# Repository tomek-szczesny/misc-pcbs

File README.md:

# misc-pcbs
Miscellaneous PCB designs

## BuLDOck

A Buck converter with LDO following it, for super clean DC output voltage. Recommended for noise sensitive applications such as audio equipment.

Designed on a single layer and with no holes, suitable for aluminum PCBs.

## ICE40HX8K-EVB Breadboard

A multipurpose breadboard that fits directly into Olimex FPGA devkit.

## PowerDistributor

A 2-layer board for DC voltage distribution. Designed for SBC cluster but might be used for anything.

Two M4 screw holes were designed to handle 30A power input. Eight pairs of screw terminals would usually serve as outputs, but that's not the law.

A center area is for properly rated capacitors - make more sense in low current applications.

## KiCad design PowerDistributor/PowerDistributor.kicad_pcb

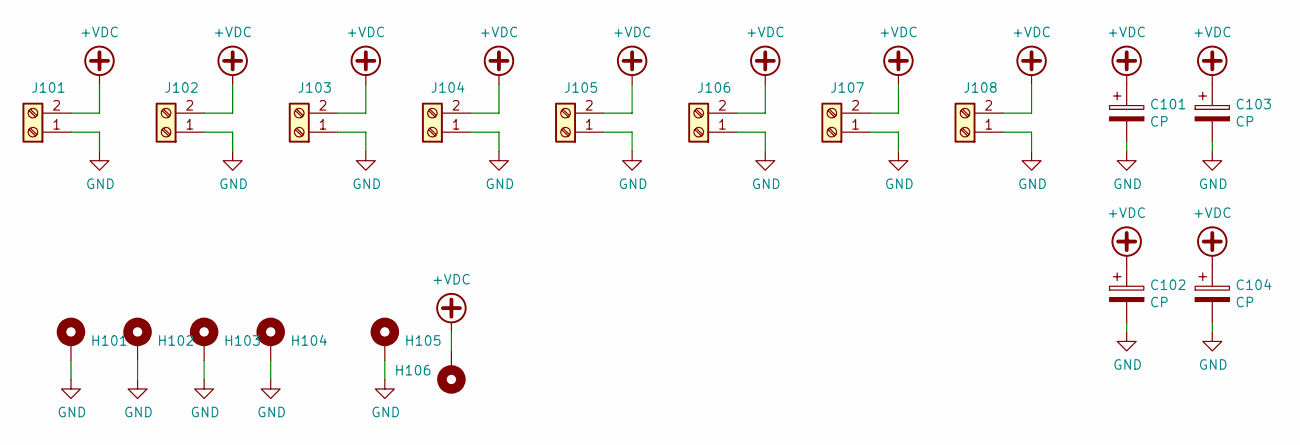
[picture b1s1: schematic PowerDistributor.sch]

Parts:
C101, C102, C103, C104: CP; CP_Radial_D10.0mm_P5.00mm
H101, H102, H103, H104: MountingHole_Pad; MountingHole_3mm_Pad_TopOnly
H105, H106: MountingHole_Pad; MountingHole_4.3mm_M4_Pad_TopBottom
J101, J102, J103, J104, J105, J106, J107, J108: Screw_Terminal_01x02; TerminalBlock_Altech_AK300-2_P5.00mm

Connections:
+VDC: C101.1, C102.1, C103.1, C104.1, H106.1, J101.2, J102.2, J103.2, J104.2, J105.2, J106.2, J107.2, J108.2
GND: C101.2, C102.2, C103.2, C104.2, H101.1, H102.1, H103.1, H104.1, H105.1, J101.1, J102.1, J103.1, J104.1, J105.1, J106.1, J107.1, J108.1

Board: 2 copper layers, 18 parts (0 on the bottom side), 2 nets, no tracks yet.

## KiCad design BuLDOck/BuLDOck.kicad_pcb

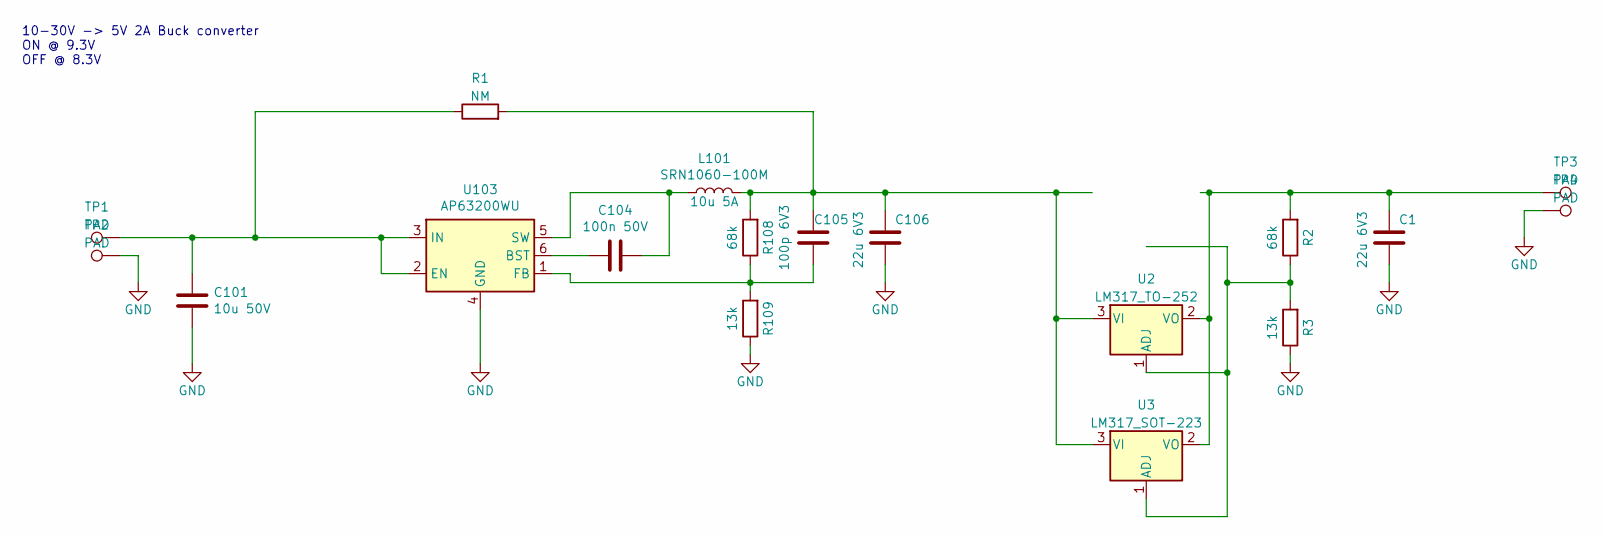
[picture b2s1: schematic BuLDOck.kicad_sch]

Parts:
C1, C106: 22u 6V3; C_1206_3216Metric
C101: 10u 50V; C_1206_3216Metric
C104: 100n 50V; C_0603_1608Metric
C105: 100p 6V3; C_0603_1608Metric
L101: SRN1060-100M; L_Bourns-SRN1060
R1: NM; R_1206_3216Metric
R2, R108: 68k; R_0603_1608Metric
R3, R109: 13k; R_0603_1608Metric
TP1, TP2, TP3, TP4: PAD; TestPoint_Pad_4.0x4.0mm
U2: LM317_TO-252; TO-252-2
U3: LM317_SOT-223; SOT-223-3_TabPin2
U103: AP63200WU; TSOT-23-6

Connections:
GND: C1.2, C101.2, C106.2, R3.1, R109.1, TP2.1, TP4.1, U103.4 (GND)
unnamed: C1.1, R2.2, TP3.1, U2.2 (VO), U3.2 (VO)
unnamed: C101.1, R1.1, TP1.1, U103.2 (EN), U103.3 (IN)
unnamed: C104.1, L101.1, U103.5 (SW)
unnamed: C104.2, U103.6 (BST)
unnamed: C105.1, C106.1, L101.2, R1.2, R108.2, U2.3 (VI), U3.3 (VI)
unnamed: C105.2, R108.1, R109.2, U103.1 (FB)
unnamed: R2.1, R3.2, U2.1 (ADJ), U3.1 (ADJ)

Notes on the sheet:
10-30V -> 5V 2A Buck converter ON @ 9.3V OFF @ 8.3V

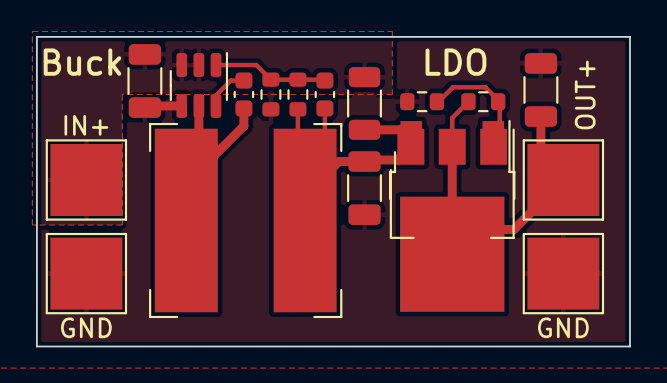
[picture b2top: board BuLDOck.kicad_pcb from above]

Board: 2 copper layers, 32.9 x 17.2 mm, 18 parts (0 on the bottom side), 8 nets.

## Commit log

2023-03-15 Initial upload of legacy projects
